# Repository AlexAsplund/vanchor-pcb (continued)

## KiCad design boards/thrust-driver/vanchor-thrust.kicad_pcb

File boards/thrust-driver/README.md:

# vanchor-thrust — trolling-motor DC driver

95×92 mm 2-layer board. Full H-bridge for a 12–24 V brushed trolling motor,
controlled by the vanchor-helm board over one straight 8-wire cable. Two
build variants share the same PCB:

| Variant | Fit | Continuous current |
|---|---|---|
| Base | U1 + U2 (2× BTN8982TA) | ~30 A (with cable reinforcement, see below) |
| High power | also U3 + U4 + R7 + R8 | ~50 A |

## Cable to the helm board

J1 mirrors helm J13 **pin-for-pin** — crimp a straight 8-wire cable
(0.5–1 mm², keep it under ~2 m, twist RPWM/LPWM with GND spares if longer):

| Pin | Signal | Direction |
|---|---|---|
| 1 | RPWM | helm → driver |
| 2 | LPWM | helm → driver |
| 3 | R_EN | helm → driver |
| 4 | L_EN | helm → driver |
| 5 | R_IS (current sense A) | driver → helm |
| 6 | L_IS (current sense B) | driver → helm |
| 7 | +5V (logic, from helm buck) | helm → driver |
| 8 | GND | — |

The LED (D1) lights when the helm's 5 V arrives — a quick cable check.

## Power wiring

M5 lugs: BATT+ / BATT− on the left edge, MOT A / MOT B on the right.
Use 10 mm² (8 AWG) or thicker cable for the 50 A build. **Fuse the battery
lead externally** (ANL or MIDI, 40 A base / 60 A high power) close to the
battery. There is **no reverse-polarity protection** — double-check
polarity before connecting; reversed battery destroys the BTN8982s.
D2 (SMCJ33A) clamps inductive spikes; the board is 12–24 V only.

## Solder-lane reinforcement (required above ~15 A continuous)

The board is ordered in standard 1 oz copper — cheap, but the copper alone
won't carry 30–50 A. Every power lane (VBAT band + spine, MOT A, MOT B on
top; GND band on the bottom) has an exposed solder lane (no solder mask).
Before first high-power use:

1. Clean the lanes with IPA, apply flux.
2. Tin each lane with a wide tip.
3. Lay 4–10 mm² desoldered copper braid or stripped solid wire along the
   lane and solder it down continuously end-to-end.

With braid on all lanes the base build handles ~30 A continuous, the
high-power build ~50 A. The 202 "solder mask bridge" DRC warnings are these
lanes — intentional.

## Firmware note (high-power variant)

Each BTN8982's IS pin sources I_load/kILIS (~8500). Both devices of a side
feed the **same** 1 k sense resistor, so with U3/U4 fitted the sensed
voltage per ampere stays the same only if the halves share evenly — in
practice treat the effective kILIS as ~22700 (verify datasheet 5.4.7) with U1/U2 only and ~17000 per
device (halved reading) when paralleled. Calibrate `THR_IS` scaling in the
Pico firmware after choosing the variant.

## NMEA2000 smart-node option (v1.1 provision, all DNP)

The board carries unpopulated through-hole provision to become a
standalone NMEA2000 node — same pattern as the helm board:

- **U5** Pico 2 (GP12-15 wired in parallel with J1's RPWM/LPWM/R_EN/L_EN,
  GP26/27 read the IS sense via R12/R13 1k series, GP18/19 run CAN via
  can2040 — identical GPIO map to the helm Pico, so the thrust firmware
  ports directly).
- **U6** SIP-3 5V regulator: R-78E5.0-0.5 for 12V boats; fit the wide-input
  **R-78HE5.0-0.5** on 24V boats (the plain R-78E tops out at 28V in, too
  close to a charging 24V bank).
- **J6** 4-pin CAN header: 3V3 / GND / TX / RX to a Waveshare SN65HVD230
  transceiver module; CAN_H/L go to the module's screw terminal.
- **J7** XH-3 lands the N2K drop cable's V+ / GND / SHIELD. R10 (0R DNP)
  optionally feeds the backbone from VBAT (fuse the drop cable); R11
  (0R DNP) bonds shield to GND at this node only if nowhere else does.

Dumb mode (default): populate nothing, drive via the J1 cable as before.
Smart mode: fit U5 + U6 + R12 + R13 + transceiver, **leave J1
unconnected** (both would drive the same nets), and implement a command
watchdog in the node firmware (hard-stop to neutral if the command PGN
stream halts >300-500 ms). ADC note: in normal operation the IS voltage
across the 1k loads stays under ~2.2V at 50A (kILIS 22.7k), but in FAULT
the IS pin sources mA-class current and the node's only protection is the
R12/R13 series resistance - fit them as 10k (not 1k) when populating the
node, or add BAT54S clamps to 3V3 like the helm board has.

## PWM frequency (firmware guidance)

The BTN8982TA allows up to 25 kHz, but this board fits **51 k slew-rate
resistors** (low-EMI edges, ~1.5 us each), so switching loss — not the
chip rating — sets the practical limit. Loss per edge scales with both
current and frequency; conduction loss at 30 A is only ~6 W, so high-kHz
PWM at high current quickly dominates the thermal budget:

```mermaid
xychart-beta
    title "Switching loss vs PWM frequency (13V, 51k SR edges ~3us total)"
    x-axis "PWM frequency (kHz)" [2, 4, 8, 12, 16, 20, 25]
    y-axis "watts" 0 --> 16
    line "at 30 A" [1.2, 2.3, 4.7, 7.0, 9.4, 11.7, 14.6]
    line "at 10 A" [0.4, 0.8, 1.6, 2.3, 3.1, 3.9, 4.9]
```

*[static SVG](../../docs/diagrams/pwm-loss.svg)*

**Recommended scheme: current-adaptive PWM.** Run high frequency where it
is silent *and* cheap (low current), ramp down as current rises so the
bridge stays efficient exactly when the prop is loud enough to mask the
hum:

```mermaid
xychart-beta
    title "Recommended PWM vs motor current"
    x-axis "motor current (A)" [0, 5, 10, 15, 20, 25, 30, 40, 50]
    y-axis "PWM frequency (kHz)" 0 --> 18
    line [16, 16, 12, 8, 6, 5, 4, 3, 2]
```

*[static SVG](../../docs/diagrams/pwm-schedule.svg)*

Implementation notes (RP2350, applies to the helm Pico driving this board
over J13 and to the on-board smart-node Pico alike):

- **Switch on measured current (IS), not throttle** — switching loss
  scales with amps. Use ~2 A hysteresis, or blend continuously per the
  curve above (nicer: the whine fades instead of stepping).
- **Glitch-free frequency changes**: change the PWM slice's wrap (TOP)
  value and rescale the compare level by the same ratio in the same
  update; both latch at the wrap boundary, so duty is preserved and the
  motor never feels a step.
- **Resolution is never the constraint**: 150 MHz / 16 kHz is still >13
  bits of duty resolution.
- **IS sampling**: if sampling mid-on-time, recompute the sample point
  when the wrap changes — or use the RC-averaged reading scaled by duty
  (frequency-agnostic; the helm's 20k + 100n chain does this).
- If the bridge runs warm at partial throttle, lower the 16 kHz band's
  ceiling (~10 A -> ~6 A) before touching hardware. If you truly need
  15-25 kHz at full current, swap R3/R4 (R7/R8) from 51 k to ~5.1 k —
  ~10x less switching loss, more EMI ringing; they are through-hole for
  exactly this experiment.

## Assembly order

1. SMD: BTN8982s (U1/U2, plus U3/U4 for high power), D2.
2. Resistors: R1–R6, R9 (+ R7/R8 with U3/U4), diode D1.
3. C3/C4 ceramics, C5 film, then C1/C2 electrolytics (mind polarity).
4. Lugs J2–J5, header J1.
5. Solder-lane braid (see above), then bolt to a heatsink/baseplate through
   the two M3 holes with a thermal pad under the BTN tabs for >20 A use.

## Ordering

Same fab spec as the helm board: 2 layers, 1.6 mm FR-4, 1 oz copper,
HASL, 5/5 mil, 0.3 mm min drill, tented vias. Upload
`fab/vanchor-thrust-gerbers.zip`. ~$10-15 for 5 pcs at PCBWay/JLC.

## Design notes / DRC deviations

- `solder_mask_bridge` warnings (~200): intentional exposed solder lanes.
- `pth/npth_inside_courtyard`, `courtyards_overlap`: warnings only, from
  the lug/cap density; verified manually.
- `solder_mask_bridge` is set to *ignore* in the project (the exposed
  solder lanes intentionally span nets' mask apertures).
- The routed .kicad_pcb includes hand-placed link tracks and via-hops for
  the DNP-pair nets (RPWM/LPWM/R_EN/L_EN/R_IS/L_IS between U1/U2 and
  U3/U4) — regenerating the board from `scripts/build_board.py` requires
  re-running freerouting **and** re-applying equivalent patches; treat the
  checked-in board file as the source of truth.

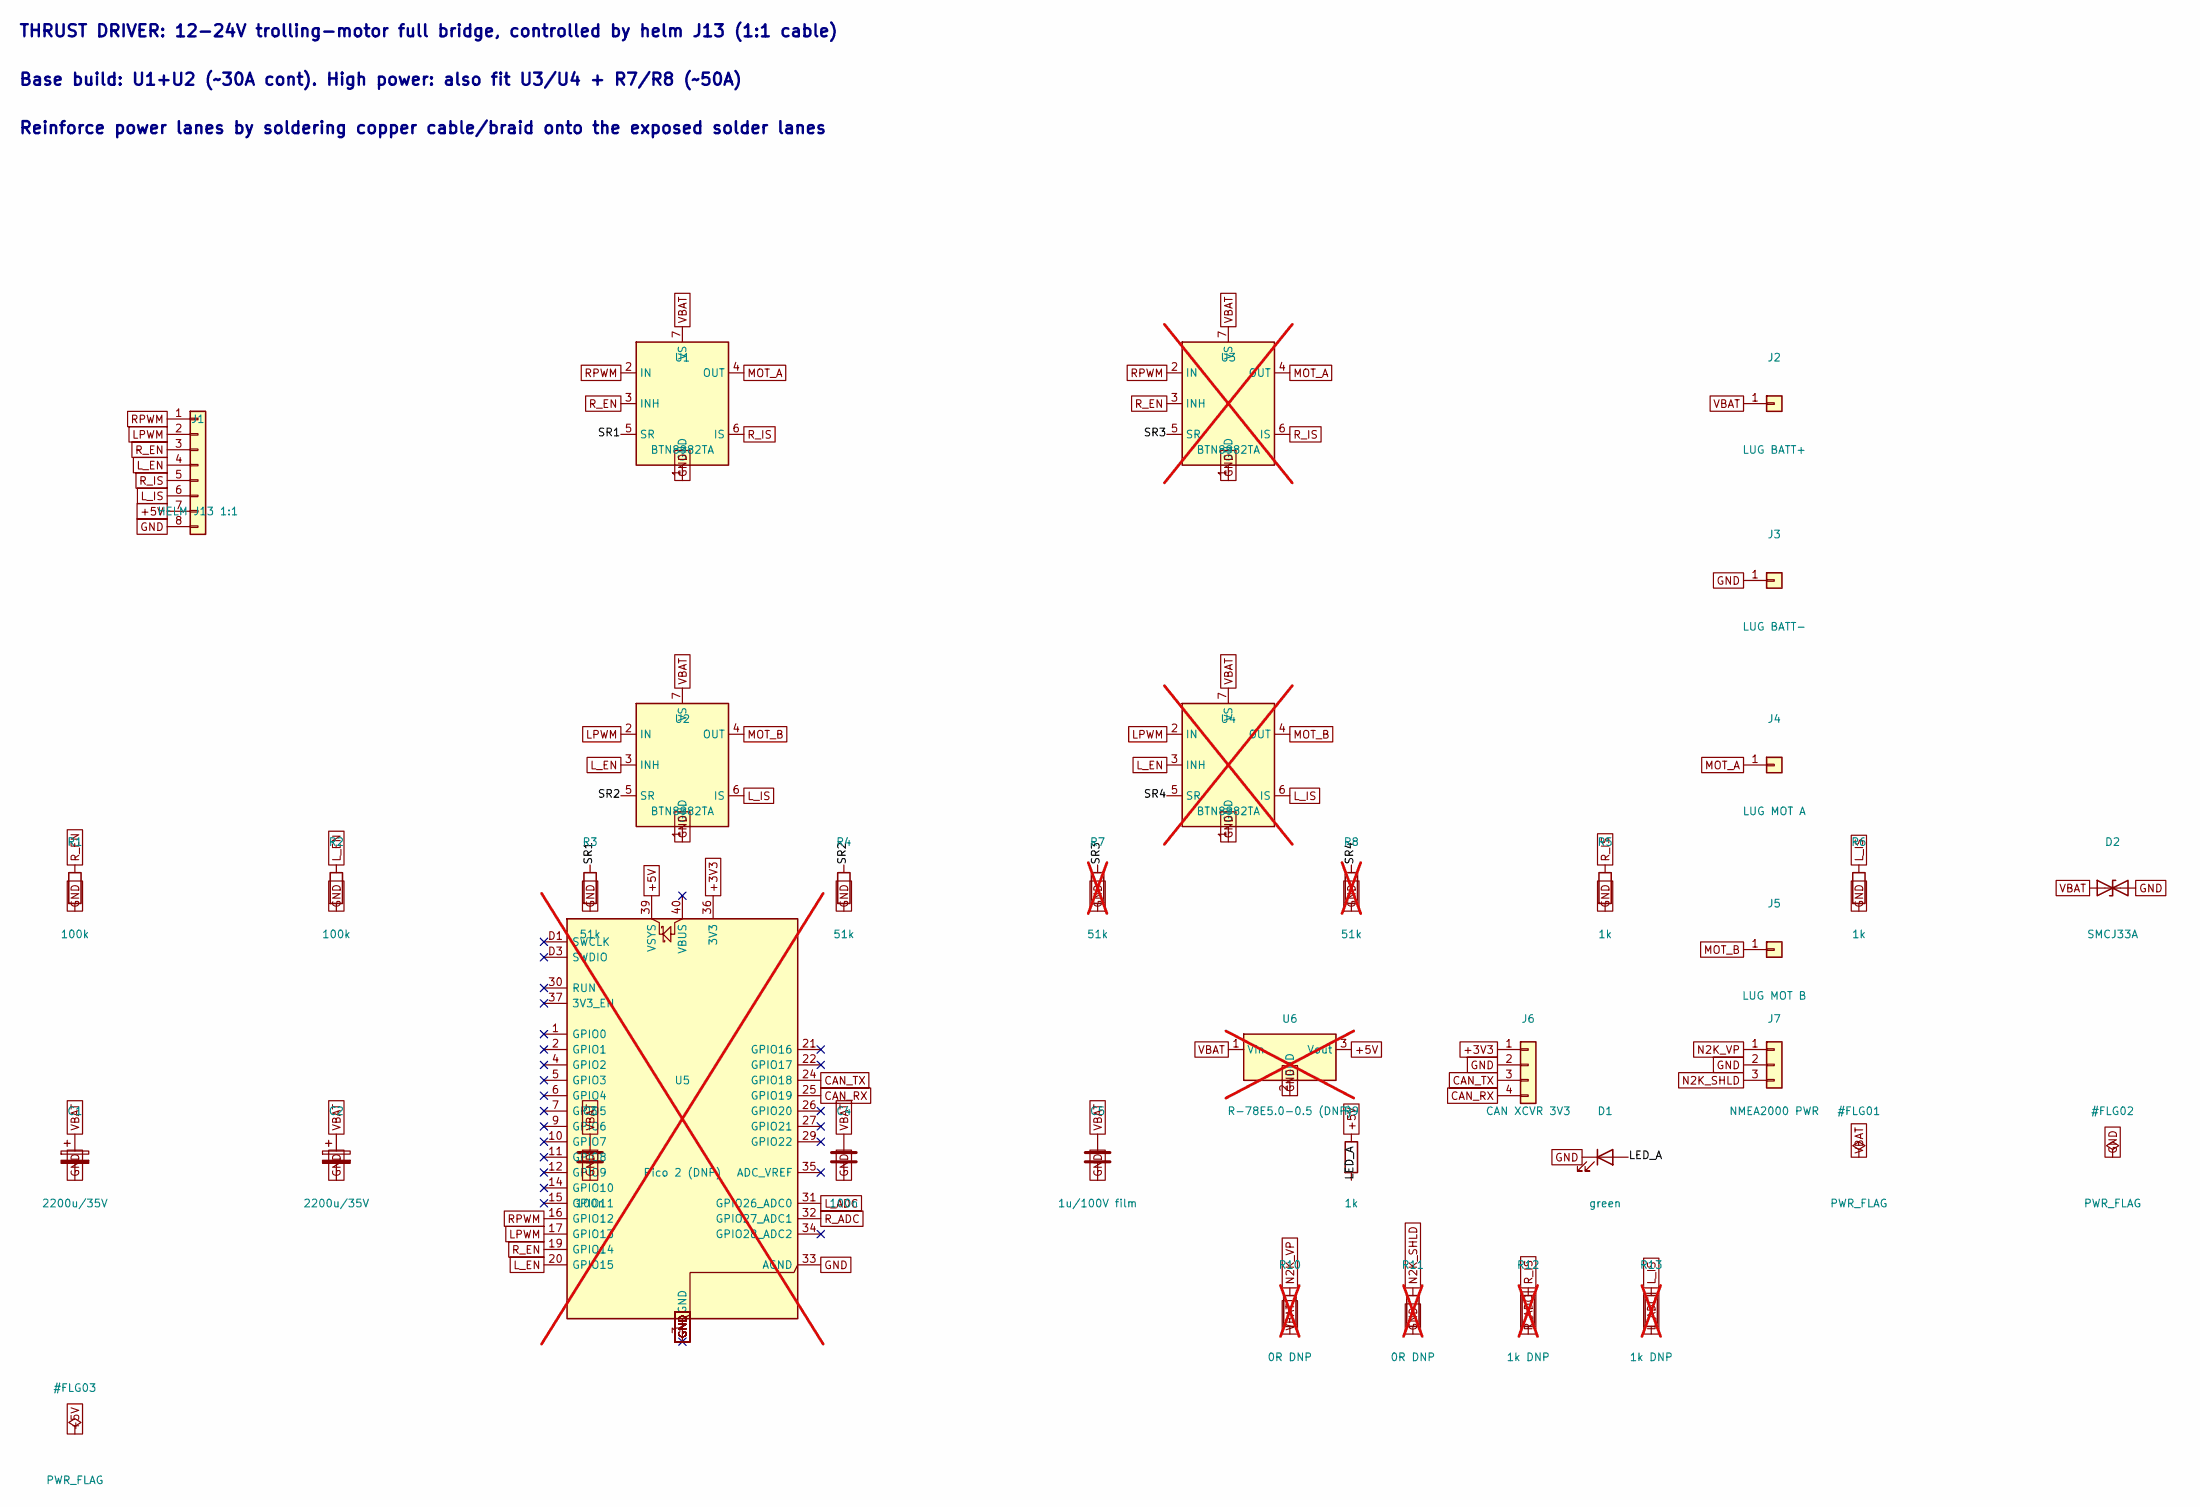
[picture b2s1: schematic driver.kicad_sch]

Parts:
C1, C2: 2200u/35V; CP_Radial_D18.0mm_P7.50mm
C3, C4: 100n; C_Disc_D5.0mm_W2.5mm_P5.00mm
C5: 1u/100V film; C_Rect_L13.0mm_W6.0mm_P10.00mm_FKS3_FKP3_MKS4
D1: green; LED_D5.0mm
D2: SMCJ33A; D_SMC
J1: HELM J13 1:1; PinHeader_1x08_P2.54mm_Vertical
J2: LUG BATT+; Lug_M5
J3: LUG BATT-; Lug_M5
J4: LUG MOT A; Lug_M5
J5: LUG MOT B; Lug_M5
J6: CAN XCVR 3V3; PinHeader_1x04_P2.54mm_Vertical
J7: NMEA2000 PWR; JST_XH_B3B-XH-A_1x03_P2.50mm_Vertical
R1, R2: 100k; R_Axial_DIN0207_L6.3mm_D2.5mm_P10.16mm_Horizontal
R3, R4: 51k; R_Axial_DIN0207_L6.3mm_D2.5mm_P10.16mm_Horizontal
R5, R6, R9: 1k; R_Axial_DIN0207_L6.3mm_D2.5mm_P10.16mm_Horizontal
R7, R8: 51k; R_Axial_DIN0207_L6.3mm_D2.5mm_P10.16mm_Horizontal; not fitted
R10, R11: 0R DNP; R_0805_2012Metric; not fitted
R12, R13: 1k DNP; R_0805_2012Metric; not fitted
U1, U2: BTN8982TA; TO-263-7_TabPin4
U3, U4: BTN8982TA; TO-263-7_TabPin4; not fitted
U5: Pico 2 (DNP); RaspberryPi_Pico_TH_SWD; not fitted
U6: R-78E5.0-0.5 (DNP); Converter_DCDC_TRACO_TSR-1_THT; not fitted

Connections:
+3V3: J6.1, U5.36 (3V3)
+5V: J1.7, R9.1, U5.39 (VSYS), U6.3 (Vout)
/driver/LED_A: D1.2 (A), R9.2
/driver/SR1: R3.1, U1.5 (SR)
/driver/SR2: R4.1, U2.5 (SR)
/driver/SR3: R7.1, U3.5 (SR)
/driver/SR4: R8.1, U4.5 (SR)
CAN_RX: J6.4, U5.25 (GPIO19)
CAN_TX: J6.3, U5.24 (GPIO18)
GND: C1.2, C2.2, C3.2, C4.2, C5.2, D1.1 (K), D2.2 (A2), J1.8, J3.1, J6.2, J7.2, R1.2, R2.2, R3.2, R4.2, R5.2, R6.2, R7.2, R8.2, R11.2, U1.1 (GND), U2.1 (GND), U3.1 (GND), U4.1 (GND), U5.3 (GND), U5.8 (GND), U5.13 (GND), U5.18 (GND), U5.23 (GND), U5.28 (GND), U5.33 (AGND), U5.38 (GND), U5.D2 (GND), U6.2 (GND)
LPWM: J1.2, U2.2 (IN), U4.2 (IN), U5.17 (GPIO13)
L_ADC: R13.2, U5.31 (GPIO26_ADC0)
L_EN: J1.4, R2.1, U2.3 (INH), U4.3 (INH), U5.20 (GPIO15)
L_IS: J1.6, R6.1, R13.1, U2.6 (IS), U4.6 (IS)
MOT_A: J4.1, U1.4 (OUT), U3.4 (OUT)
MOT_B: J5.1, U2.4 (OUT), U4.4 (OUT)
N2K_SHLD: J7.3, R11.1
N2K_VP: J7.1, R10.1
RPWM: J1.1, U1.2 (IN), U3.2 (IN), U5.16 (GPIO12)
R_ADC: R12.2, U5.32 (GPIO27_ADC1)
R_EN: J1.3, R1.1, U1.3 (INH), U3.3 (INH), U5.19 (GPIO14)
R_IS: J1.5, R5.1, R12.1, U1.6 (IS), U3.6 (IS)
VBAT: C1.1, C2.1, C3.1, C4.1, C5.1, D2.1 (A1), J2.1, R10.2, U1.7 (VS), U2.7 (VS), U3.7 (VS), U4.7 (VS), U6.1 (Vin)

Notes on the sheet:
THRUST DRIVER: 12-24V trolling-motor full bridge, controlled by helm J13 (1:1 cable)
Base build: U1+U2 (~30A cont). High power: also fit U3/U4 + R7/R8 (~50A)
Reinforce power lanes by soldering copper cable/braid onto the exposed solder lanes

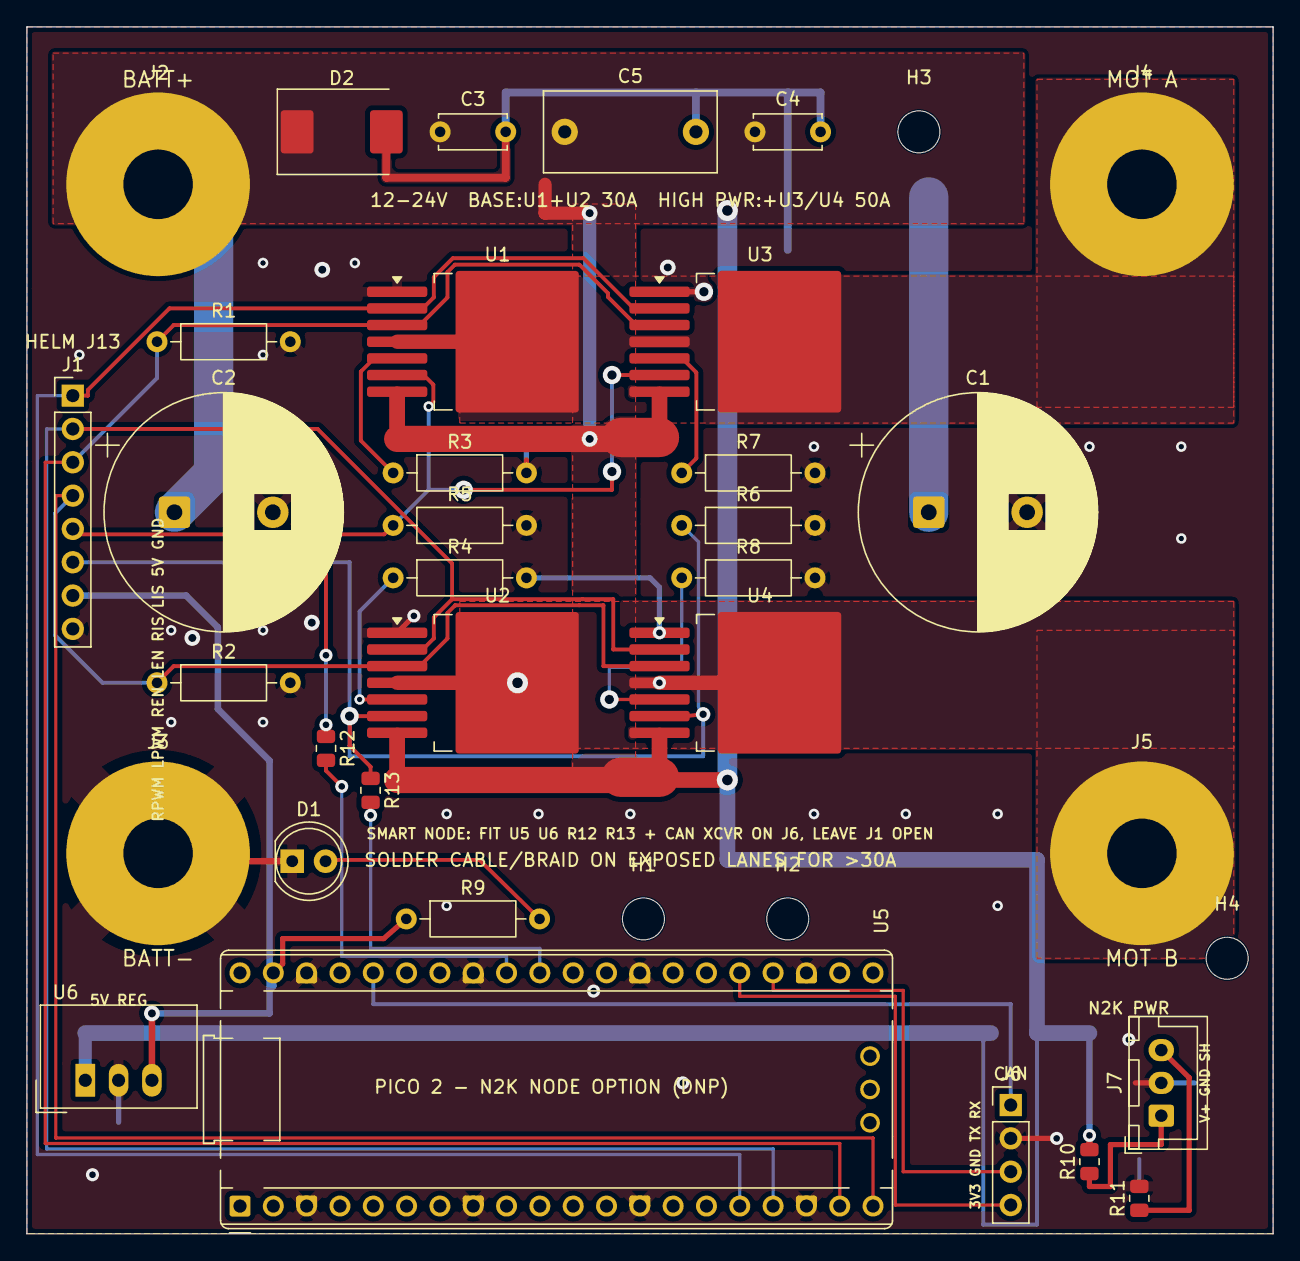
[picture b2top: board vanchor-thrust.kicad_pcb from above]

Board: 2 copper layers, 95.0 x 92.0 mm, 37 parts (0 on the bottom side), 23 nets.

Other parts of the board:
H1, H2: MountingHole_3.2mm_M3
H3, H4: MountingHole; MountingHole_3.2mm_M3

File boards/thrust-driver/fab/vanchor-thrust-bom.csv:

"Ref","Value","Footprint","MPN","Qty","DNP"
"C1,C2","2200u/35V","Capacitor_THT:CP_Radial_D18.0mm_P7.50mm","","2",""
"C3,C4","100n","Capacitor_THT:C_Disc_D5.0mm_W2.5mm_P5.00mm","","2",""
"C5","1u/100V film","Capacitor_THT:C_Rect_L13.0mm_W6.0mm_P10.00mm_FKS3_FKP3_MKS4","","1",""
"D1","green","LED_THT:LED_D5.0mm","","1",""
"D2","SMCJ33A","Diode_SMD:D_SMC","","1",""
"J1","HELM J13 1:1","Connector_PinHeader_2.54mm:PinHeader_1x08_P2.54mm_Vertical","","1",""
"J2","LUG BATT+","vanchor-helm:Lug_M5","","1",""
"J3","LUG BATT-","vanchor-helm:Lug_M5","","1",""
"J4","LUG MOT A","vanchor-helm:Lug_M5","","1",""
"J5","LUG MOT B","vanchor-helm:Lug_M5","","1",""
"J6","CAN XCVR 3V3","Connector_PinHeader_2.54mm:PinHeader_1x04_P2.54mm_Vertical","","1",""
"J7","NMEA2000 PWR","Connector_JST:JST_XH_B3B-XH-A_1x03_P2.50mm_Vertical","","1",""
"R1,R2","100k","Resistor_THT:R_Axial_DIN0207_L6.3mm_D2.5mm_P10.16mm_Horizontal","","2",""
"R3,R4,R7,R8","51k","Resistor_THT:R_Axial_DIN0207_L6.3mm_D2.5mm_P10.16mm_Horizontal","","4","DNP"
"R5,R6,R9","1k","Resistor_THT:R_Axial_DIN0207_L6.3mm_D2.5mm_P10.16mm_Horizontal","","3",""
"R10,R11","0R DNP","Resistor_SMD:R_0805_2012Metric","","2","DNP"
"R12,R13","1k DNP","Resistor_SMD:R_0805_2012Metric","","2","DNP"
"U1-U4","BTN8982TA","Package_TO_SOT_SMD:TO-263-7_TabPin4","","4","DNP"
"U5","Pico 2 (DNP)","vanchor-helm:RaspberryPi_Pico_TH_SWD","","1","DNP"
"U6","R-78E5.0-0.5 (DNP)","Converter_DCDC:Converter_DCDC_TRACO_TSR-1_THT","","1","DNP"

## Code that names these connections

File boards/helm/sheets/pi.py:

"""Orange Pi Zero 3 carrier sheet (v4): 26-pin socket, UART JSTs, spare I2C,
fan, fused aux 5V.

J1 = 2x13 MALE header; the Zero 3 (pre-soldered pins-up variant) connects
via a standard 26-way 1:1 IDC ribbon (original-RPi style). Module is
powered THROUGH the ribbon 5V pins from the on-board buck — no USB-C.
J2 = 1:1 breakout of all 26 pins (DNP). The net map follows the CLASSIC
Raspberry Pi 26-pin positions (the Zero 3 header mimics it), so J2 doubles
as an alternate SBC port: ribbon a Raspberry Pi (pins 1-26 of the 40-pin
header, aligned at pin 1) instead of the Orange Pi. Power, I2C link to the
Pico (RPi SDA1/SCL1), console UART (RPi TXD0/RXD0), SPI and the SWD/RUN
GPIOs all land on equivalent RPi pins. Caveats: fit ONE SBC only (J1 and
J2 share the bus); on an RPi, pins 11/13 (J4 "UART2" JST) are plain GPIOs
- no hardware UART there, use bit-bang or skip J4.

The Zero 3's 26-pin header exposes two usable UARTs (UART5 on PH2/PH3,
UART2 on PC5/PC6) plus TWI3 (I2C) — the Pico link rides TWI3. The H618
debug UART lives on the module's own separate 3-pin header. SWD reflash of
the Pico uses two PC GPIOs (pins 16/18); PICO RUN on pin 12.
"""
from common import HDR2x13, XH2, XH4, HDR1x2, R_AX, LED5MM, POLYFUSE, grid

SHEET_UUID = "c0000000-0000-4000-8000-000000000003"

TEXTS = [
    (30, 40, "ORANGE PI ZERO 3 CARRIER: J1 male header -> 26-way IDC ribbon to the module"),
    (30, 46, "Module is powered through header 5V pins - do NOT also plug USB-C power"),
    (30, 52, "UART TX/RX directions per OPi manual - if a device stays silent, swap TX/RX at the JST"),
    (30, 58, "J2 = same bus, classic RPi 26-pin positions: fits a Raspberry Pi (40-pin header pins 1-26). ONE SBC only"),
]

# Orange Pi Zero 3 26-pin header net map (H618 port in comments)
PI26 = {
    "1": "3V3_PI", "2": "+5V",
    "3": "PI_SDA",            # PH5  TWI3-SDA -> Pico
    "4": "+5V",
    "5": "PI_SCL",            # PH4  TWI3-SCK -> Pico
    "6": "GND",
    "7": "OPI_PC9",
    "8": "UART5_TX",          # PH2
    "9": "GND",
    "10": "UART5_RX",         # PH3
    "11": "UART2_TX",         # PC6 (check DT overlay; swap at JST if needed)
    "12": "PI_PICO_RUN",      # PC11 -> Pico RUN (reset)
    "13": "UART2_RX",         # PC5
    "14": "GND",
    "15": "OPI_PC8",
    "16": "PI_GPIO24",        # PC15 -> Pico SWDIO
    "17": "3V3_PI",
    "18": "PI_GPIO25",        # PC14 -> Pico SWCLK
    "19": "OPI_MOSI",         # PH7  SPI1
    "20": "GND",
    "21": "OPI_MISO",         # PH8
    "22": "OPI_PC7",
    "23": "OPI_SCLK",         # PH6
    "24": "OPI_CS",           # PH9
    "25": "GND",
    "26": "OPI_PC10",
}

# Ground economy: J1.14, J1.20 and J2.9 are deliberately NC — each connector keeps
# four other GND pins (6/9/20/25 resp. 6/14/20/25); the escape routing under
# the header field claims those two pads' corridors.
J1_PINS = dict(PI26, **{"14": None, "20": None})
J2_PINS = dict(PI26, **{"9": None})

COMPONENTS = [
    dict(lib="Connector_Generic:Conn_02x13_Odd_Even", ref="J1", value="OPI_Z3_26PIN",
         fp=HDR2x13, at=(70, 95, 0), pins=J1_PINS),
    dict(lib="Connector_Generic:Conn_02x13_Odd_Even", ref="J2", value="SBC2_OPI_RPI26", dnp=True,
         fp=HDR2x13, at=(150, 95, 0), pins=J2_PINS),

    dict(lib="Connector_Generic:Conn_01x04", ref="J3", value="UART5 ttyAS5", fp=XH4,
         at=(230, 70, 0), pins={"1": "3V3_PI", "2": "UART5_TX", "3": "UART5_RX", "4": "GND"}),
    dict(lib="Connector_Generic:Conn_01x04", ref="J4", value="UART2 ttyAS2", fp=XH4,
         at=(260, 70, 0), pins={"1": "3V3_PI", "2": "UART2_TX", "3": "UART2_RX", "4": "GND"}),

    dict(lib="Connector_Generic:Conn_01x04", ref="J8", value="I2C3 spare", fp=XH4,
         at=(230, 120, 0), pins={"1": "3V3_PI", "2": "PI_SDA", "3": "PI_SCL", "4": "GND"}),
    dict(lib="Device:R", ref="R5", value="2.2k", fp=R_AX, dnp=True,
         at=(260, 120, 0), pins={"1": "3V3_PI", "2": "PI_SDA"}),
    dict(lib="Device:R", ref="R6", value="2.2k", fp=R_AX, dnp=True,
         at=(290, 120, 0), pins={"1": "3V3_PI", "2": "PI_SCL"}),

    dict(lib="Connector_Generic:Conn_01x03", ref="J9", value="FAN + HALL",
         fp="Connector_PinHeader_2.54mm:PinHeader_1x03_P2.54mm_Vertical",
         at=(320, 120, 0), pins={"1": "+5V", "2": "GND", "3": "HALL_ZERO"}),
    dict(lib="Device:Polyfuse", ref="F2", value="MF-R250 2.5A", fp=POLYFUSE,
         at=(350, 120, 0), pins={"1": "+5V", "2": "DISP_5V"}),
    dict(lib="Connector_Generic:Conn_01x02", ref="J10", value="AUX 5V (screen)", fp=XH2,
         at=(380, 120, 0), pins={"1": "DISP_5V", "2": "GND"}),

    dict(lib="power:PWR_FLAG", ref="#FLG04", value="PWR_FLAG",
         at=grid(2), pins={"1": "3V3_PI"}),
]

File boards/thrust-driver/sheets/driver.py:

"""Thrust driver board: 12-24V full-bridge for the trolling motor.

One sheet. J1 mirrors the helm board's J13 pin-for-pin (IBT-2 order), so a
straight 8-wire cable connects them. U1/U2 = base bridge (~30A cont);
U3/U4 + their SR resistors = DNP parallel pair for the high-power build
(fit for ~50A sustained; both pairs share IN/INH, each device has its own
slew-rate resistor; IS current sources sum into the shared 1k loads so the
helm's telemetry scaling is unchanged per-variant... halved kILIS effective
- note in firmware calibration).
"""
from common import R_AX, C_D, CP_BULK, SMC, TO263_7, HDR1x8, LED5MM, LUG, FILM, grid

SHEET_UUID = "d0000000-0000-4000-8000-000000000002"

TEXTS = [
    (30, 30, "THRUST DRIVER: 12-24V trolling-motor full bridge, controlled by helm J13 (1:1 cable)"),
    (30, 38, "Base build: U1+U2 (~30A cont). High power: also fit U3/U4 + R7/R8 (~50A)"),
    (30, 46, "Reinforce power lanes by soldering copper cable/braid onto the exposed solder lanes"),
]

COMPONENTS = [
    # control interface - identical pinout to helm J13
    dict(lib="Connector_Generic:Conn_01x08", ref="J1", value="HELM J13 1:1", fp=HDR1x8,
         at=(45, 95, 0), pins={
            "1": "RPWM", "2": "LPWM", "3": "R_EN", "4": "L_EN",
            "5": "R_IS", "6": "L_IS", "7": "+5V", "8": "GND"}),
    dict(lib="Device:R", ref="R1", value="100k", fp=R_AX,
         at=(130, 195, 90), pins={"1": "R_EN", "2": "GND"}),
    dict(lib="Device:R", ref="R2", value="100k", fp=R_AX,
         at=(174, 195, 90), pins={"1": "L_EN", "2": "GND"}),

    # base bridge
    dict(lib="vanchor-helm:BTN8982TA", ref="U1", value="BTN8982TA", fp=TO263_7,
         at=(135, 80, 0), pins={"1": "GND", "2": "RPWM", "3": "R_EN",
                                "4": "MOT_A", "5": ".SR1", "6": "R_IS", "7": "VBAT"}),
    dict(lib="vanchor-helm:BTN8982TA", ref="U2", value="BTN8982TA", fp=TO263_7,
         at=(135, 150, 0), pins={"1": "GND", "2": "LPWM", "3": "L_EN",
                                 "4": "MOT_B", "5": ".SR2", "6": "L_IS", "7": "VBAT"}),
    dict(lib="Device:R", ref="R3", value="51k", fp=R_AX,
         at=(218, 195, 90), pins={"1": ".SR1", "2": "GND"}),
    dict(lib="Device:R", ref="R4", value="51k", fp=R_AX,
         at=(262, 195, 90), pins={"1": ".SR2", "2": "GND"}),

    # high-power parallel pair (DNP on base builds)
    dict(lib="vanchor-helm:BTN8982TA", ref="U3", value="BTN8982TA", fp=TO263_7, dnp=True,
         at=(225, 80, 0), pins={"1": "GND", "2": "RPWM", "3": "R_EN",
                                "4": "MOT_A", "5": ".SR3", "6": "R_IS", "7": "VBAT"}),
    dict(lib="vanchor-helm:BTN8982TA", ref="U4", value="BTN8982TA", fp=TO263_7, dnp=True,
         at=(225, 150, 0), pins={"1": "GND", "2": "LPWM", "3": "L_EN",
                                 "4": "MOT_B", "5": ".SR4", "6": "L_IS", "7": "VBAT"}),
    dict(lib="Device:R", ref="R7", value="51k", fp=R_AX, dnp=True,
         at=(306, 195, 90), pins={"1": ".SR3", "2": "GND"}),
    dict(lib="Device:R", ref="R8", value="51k", fp=R_AX, dnp=True,
         at=(130, 220, 90), pins={"1": ".SR4", "2": "GND"}),

    # IS loads: current-source outputs develop the sense voltage here
    dict(lib="Device:R", ref="R5", value="1k", fp=R_AX,
         at=(174, 220, 90), pins={"1": "R_IS", "2": "GND"}),
    dict(lib="Device:R", ref="R6", value="1k", fp=R_AX,
         at=(218, 220, 90), pins={"1": "L_IS", "2": "GND"}),

    # power conditioning
    dict(lib="Device:D_TVS", ref="D2", value="SMCJ33A", fp=SMC,
         at=(322, 190, 0), pins={"1": "VBAT", "2": "GND"}),
    dict(lib="Device:C_Polarized", ref="C1", value="2200u/35V", fp=CP_BULK,
         at=(218, 245, 90), pins={"1": "VBAT", "2": "GND"}),
    dict(lib="Device:C_Polarized", ref="C2", value="2200u/35V", fp=CP_BULK,
         at=(258, 245, 90), pins={"1": "VBAT", "2": "GND"}),
    dict(lib="Device:C", ref="C3", value="100n", fp=C_D,
         at=(262, 220, 90), pins={"1": "VBAT", "2": "GND"}),
    dict(lib="Device:C", ref="C4", value="100n", fp=C_D,
         at=(306, 220, 90), pins={"1": "VBAT", "2": "GND"}),
    dict(lib="Device:C", ref="C5", value="1u/100V film", fp=FILM,
         at=(130, 245, 90), pins={"1": "VBAT", "2": "GND"}),

    # cable-live indicator off the helm's 5V
    dict(lib="Device:R", ref="R9", value="1k", fp=R_AX,
         at=(174, 245, 90), pins={"1": "+5V", "2": ".LED_A"}),
    dict(lib="Device:LED", ref="D1", value="green", fp=LED5MM,
         at=(374, 168, 0), pins={"2": ".LED_A", "1": "GND"}),

    # ---- NMEA2000 node provision (ALL DNP: holes only, populate later) ----
    # Smart-node mode: fit U5 (Pico 2), U6 (TSR-1/R-78E5.0 SIP-3 regulator),
    # R12/R13 (1k ADC series) and a 3.3V CAN transceiver on J6; the node then
    # self-powers from VBAT and takes commands over NMEA2000 (can2040 on
    # GP18/GP19). Leave J1 unconnected in that mode. Dumb mode: leave all of
    # this unpopulated and drive via J1 as today. Same GPIO map as the helm
    # Pico: GP12-15 drive, GP26/27 sense, GP18/19 CAN.
    dict(lib="MCU_Module:RaspberryPi_Pico_Debug", ref="U5", value="Pico 2 (DNP)", dnp=True,
         fp="vanchor-helm:RaspberryPi_Pico_TH_SWD",
         at=(70, 238, 0), pins={
            "3": "GND", "8": "GND", "13": "GND", "18": "GND", "23": "GND",
            "28": "GND", "33": "GND", "38": "GND",
            "16": "RPWM", "17": "LPWM", "19": "R_EN", "20": "L_EN",
            "24": "CAN_TX", "25": "CAN_RX",
            "31": "L_ADC", "32": "R_ADC",
            "36": "+3V3", "39": "+5V",
            **{str(n): None for n in (1, 2, 4, 5, 6, 7, 9, 10, 11, 12, 14, 15,
                                      21, 22, 26, 27, 29, 30, 34, 35, 37, 40)},
            "D1": None, "D2": None, "D3": None}),
    dict(lib="Converter_DCDC:TSR_1-2450", ref="U6", value="R-78E5.0-0.5 (DNP)", dnp=True,
         fp="Converter_DCDC:Converter_DCDC_TRACO_TSR-1_THT",
         at=(374, 195, 0), pins={"1": "VBAT", "2": "GND", "3": "+5V"}),
    dict(lib="Connector_Generic:Conn_01x04", ref="J6", value="CAN XCVR 3V3", fp=HDR1x8.replace("1x08", "1x04"),
         at=(330, 222, 0), pins={"1": "+3V3", "2": "GND", "3": "CAN_TX", "4": "CAN_RX"}),
    dict(lib="Connector_Generic:Conn_01x03", ref="J7", value="NMEA2000 PWR",
         fp="Connector_JST:JST_XH_B3B-XH-A_1x03_P2.50mm_Vertical",
         at=(374, 222, 0), pins={"1": "N2K_VP", "2": "GND", "3": "N2K_SHLD"}),
    dict(lib="Device:R", ref="R10", value="0R DNP", dnp=True,
         fp="Resistor_SMD:R_0805_2012Metric",
         at=(130, 267, 90), pins={"1": "N2K_VP", "2": "VBAT"}),
    dict(lib="Device:R", ref="R11", value="0R DNP", dnp=True,
         fp="Resistor_SMD:R_0805_2012Metric",
         at=(172, 267, 90), pins={"1": "N2K_SHLD", "2": "GND"}),
    dict(lib="Device:R", ref="R12", value="1k DNP", dnp=True,
         fp="Resistor_SMD:R_0805_2012Metric",
         at=(214, 267, 90), pins={"1": "R_IS", "2": "R_ADC"}),
    dict(lib="Device:R", ref="R13", value="1k DNP", dnp=True,
         fp="Resistor_SMD:R_0805_2012Metric",
         at=(254, 267, 90), pins={"1": "L_IS", "2": "L_ADC"}),

    # power lugs
    dict(lib="Connector_Generic:Conn_01x01", ref="J2", value="LUG BATT+", fp=LUG,
         at=(330, 75, 0), pins={"1": "VBAT"}),
    dict(lib="Connector_Generic:Conn_01x01", ref="J3", value="LUG BATT-", fp=LUG,
         at=(330, 105, 0), pins={"1": "GND"}),
    dict(lib="Connector_Generic:Conn_01x01", ref="J4", value="LUG MOT A", fp=LUG,
         at=(330, 135, 0), pins={"1": "MOT_A"}),
    dict(lib="Connector_Generic:Conn_01x01", ref="J5", value="LUG MOT B", fp=LUG,
         at=(330, 165, 0), pins={"1": "MOT_B"}),

    dict(lib="power:PWR_FLAG", ref="#FLG01", value="PWR_FLAG",
         at=(330, 42, 0), pins={"1": "VBAT"}),
    dict(lib="power:PWR_FLAG", ref="#FLG02", value="PWR_FLAG",
         at=(352, 42, 0), pins={"1": "GND"}),
    dict(lib="power:PWR_FLAG", ref="#FLG03", value="PWR_FLAG",
         at=(374, 42, 0), pins={"1": "+5V"}),
]

WIRES = [
    # DNP Pico smart-node hookup: CAN pair to the transceiver header,
    # IS sense through the 1k series resistors to the ADCs
    (("U5", "24"), ("J6", "3"), [("x", 106.68), ("y", 280.67), ("x", 283.21), ("y", 223.27)]),
    (("U5", "25"), ("J6", "4"), [("x", 104.14), ("y", 283.21), ("x", 287.02), ("y", 225.81)]),
    (("U5", "31"), ("R13", "2"), [("x", 111.76), ("y", 262.89)]),
    (("U5", "32"), ("R12", "2"), [("x", 109.22), ("y", 264.16)]),
]

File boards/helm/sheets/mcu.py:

"""Pico 2 controller sheet: I2C slave to Pi, I2C master to AS5600, PWM to
H-bridge, digipot/contactor control lines, battery telemetry, utility header.

Pin allocation per plan (Pico 2 module is pin-compatible with the Pico symbol).
"""
from common import PICO_FP, R_AX, C_D, SOT23, LED5MM, HDR1x8, grid

SHEET_UUID = "c0000000-0000-4000-8000-000000000004"

TEXTS = [
    (30, 40, "MCU: Pico 2 (RP2350) - I2C0 slave @0x42 to Pi, I2C1 master to AS5600"),
    (30, 46, "Firmware map: 0x00 CMD {pwm,dir,steer} / 0x10 STATUS {angle,ok,wrap,state,vbat,isense}; 800ms watchdog"),
    (30, 52, "Pico soldered directly (low profile, sits under the Pi). Pi reflashes it via SWD on GPIO24/25 (openocd)."),
]

COMPONENTS = [
    dict(lib="MCU_Module:RaspberryPi_Pico_Debug", ref="U1", value="Pico 2", fp=PICO_FP,
         at=(80, 110, 0), pins={
            "1": "PICO_GP0", "2": "PICO_GP1", "3": "GND",
            "4": "PICO_GP2", "5": "PICO_GP3",
            "6": "PI_SDA", "7": "PI_SCL", "8": "GND",
            "9": "ENC_SDA", "10": "ENC_SCL",
            "11": "RPWM", "12": "LPWM", "13": "GND",
            "14": "R_EN", "15": "L_EN",
            "16": "THR_RPWM", "17": "THR_LPWM", "18": "GND",
            "19": "THR_R_EN", "20": "THR_L_EN",
            "21": None, "22": "LED_STAT", "23": "GND",
            "24": "PICO_GP18", "25": "PICO_GP19", "26": None,
            "27": None, "28": "GND", "29": None,  # GP20-22 unused
            "30": ".PICO_RUN",
            "31": "SERVO_IS", "32": "THR_IS",
            "33": "GND", "34": "VBAT_SENSE",
            "35": None,          # ADC_VREF: module's onboard filter
            "36": "+3V3", "37": None,  # 3V3_EN: pulled up on module
            "38": "GND", "39": "+5V", "40": None,  # VBUS unused (no USB power in)
            "D1": "PI_GPIO25",   # SWCLK <- Pi (openocd bcm2835gpio reflash)
            "D2": "GND",
            "D3": "PI_GPIO24",   # SWDIO <-> Pi
         }),

    dict(lib="Device:R", ref="R8", value="1k", fp=R_AX,
         at=grid(0), pins={"1": "PI_PICO_RUN", "2": ".PICO_RUN"}),
    dict(lib="Device:R", ref="R9", value="4.7k", fp=R_AX,
         at=grid(1), pins={"1": "+3V3", "2": "ENC_SDA"}),
    dict(lib="Device:R", ref="R10", value="4.7k", fp=R_AX,
         at=grid(2), pins={"1": "+3V3", "2": "ENC_SCL"}),

    # Battery voltage telemetry: 47k/10k = /5.7 -> 14.4V charging reads 2.53V
    dict(lib="Device:R", ref="R11", value="47k", fp=R_AX,
         at=grid(3), pins={"1": "VIN", "2": "VBAT_SENSE"}),
    dict(lib="Device:R", ref="R12", value="10k", fp=R_AX,
         at=grid(4), pins={"1": "VBAT_SENSE", "2": "GND"}),
    dict(lib="Device:C", ref="C5", value="100n", fp=C_D,
         at=grid(5), pins={"1": "VBAT_SENSE", "2": "GND"}),
    dict(lib="Diode:BAT54S", ref="D6", value="BAT54S", fp=SOT23,
         at=grid(6), pins={"1": "GND", "2": "+3V3", "3": "VBAT_SENSE"}),

    dict(lib="Device:R", ref="R13", value="1k", fp=R_AX,
         at=grid(7), pins={"1": "LED_STAT", "2": ".LED5_A"}),
    dict(lib="Device:LED", ref="LED5", value="yellow", fp=LED5MM,
         at=grid(8), pins={"2": ".LED5_A", "1": "GND"}),

    # steering zero/index hall switch (A3144 class, open collector) shares
    # J9 (FAN header grows 1x2 -> 1x3: 5V GND SIG). 10k pullup to 3V3 (the
    # line can never exceed 3V3), 100n filter, 1k series into GP0 (also on J12.2
    # as a breakout/test point; UART0 fallback moves to GP16/GP1).
    dict(lib="Device:R", ref="R22", value="10k",
         fp="Resistor_SMD:R_0805_2012Metric",
         at=(230, 150, 0), pins={"1": "HALL_ZERO", "2": "+3V3"}),
    dict(lib="Device:R", ref="R23", value="1k",
         fp="Resistor_SMD:R_0805_2012Metric",
         at=(260, 150, 0), pins={"1": "HALL_ZERO", "2": "PICO_GP0"}),
    dict(lib="Device:C", ref="C24", value="100n",
         fp="Capacitor_SMD:C_0805_2012Metric",
         at=(290, 150, 0), pins={"1": "HALL_ZERO", "2": "GND"}),

    dict(lib="Connector_Generic:Conn_01x08", ref="J12", value="PICO UTIL", fp=HDR1x8, dnp=True,
         at=(200, 110, 0), pins={
            "1": "+3V3", "2": "PICO_GP0", "3": "PICO_GP1", "4": "PICO_GP2",
            "5": "PICO_GP3", "6": "PICO_GP18", "7": "PICO_GP19", "8": "GND"}),
]

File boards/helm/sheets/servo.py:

"""Servo sheet: ON-BOARD H-bridge (2x BTN8982TA half-bridges) for the 12V worm
gearmotor + the cabled AS5600 encoder connector (I2C1).

The BTN8982 pair speaks the exact BTS7960/IBT-2 interface the vanchor-ng
steering firmware already uses: RPWM/LPWM into IN, R_EN/L_EN into INH,
combined IS through one 1k sense resistor (only the driving side sources
current) filtered + clamped into the Pico ADC. VM = +12V rail.
"""
from common import XH2, XH4, TB2, R_AX, C_D, SOT23, grid

SHEET_UUID = "c0000000-0000-4000-8000-000000000006"

TEXTS = [
    (30, 40, "SERVO: on-board 2x BTN8982TA half-bridge (BTS7960-compatible interface), VM = +12V rail"),
    (30, 46, "AS5600 (in servo housing per vanchor-ng cad/) cabled to J11; keep lead <1m, 100kHz"),
    (30, 52, "24-48V boats: servo stall limited by BUCK2 (4.5A). 12V boats: J17 links VIN->12V, full stall current"),
]

COMPONENTS = [
    dict(lib="vanchor-helm:BTN8982TA", ref="U7", value="BTN8982TA",
         fp="Package_TO_SOT_SMD:TO-263-7_TabPin4",
         at=(70, 100, 0), pins={
            "1": "GND", "2": "RPWM", "3": "R_EN",
            "4": "SERVO_A", "5": ".SR_A", "6": ".SERVO_IS_RAW", "7": "VIN"}),
    dict(lib="vanchor-helm:BTN8982TA", ref="U8", value="BTN8982TA",
         fp="Package_TO_SOT_SMD:TO-263-7_TabPin4",
         at=(130, 100, 0), pins={
            "1": "GND", "2": "LPWM", "3": "L_EN",
            "4": "SERVO_B", "5": ".SR_B", "6": ".SERVO_IS_RAW", "7": "VIN"}),
    dict(lib="Device:R", ref="R39", value="47k", fp=R_AX,     # slew-rate set
         at=grid(0), pins={"1": ".SR_A", "2": "GND"}),
    dict(lib="Device:R", ref="R40", value="47k", fp=R_AX,
         at=grid(1), pins={"1": ".SR_B", "2": "GND"}),
    dict(lib="Device:C_Polarized", ref="C22", value="220u/25V",
         fp="Capacitor_THT:CP_Radial_D8.0mm_P3.50mm",
         at=grid(2), pins={"1": "VIN", "2": "GND"}),
    dict(lib="Device:C", ref="C23", value="100n", fp=C_D,
         at=grid(3), pins={"1": "VIN", "2": "GND"}),
    dict(lib="Connector_Generic:Conn_01x02", ref="J22", value="SERVO MOTOR", fp=TB2,
         at=(200, 100, 0), pins={"1": "SERVO_A", "2": "SERVO_B"}),

    # combined current sense: IS pins -> 1k to GND, filtered + clamped to ADC
    dict(lib="Device:R", ref="R19", value="1k", fp=R_AX,
         at=grid(4), pins={"1": ".SERVO_IS_RAW", "2": "GND"}),
    dict(lib="Device:R", ref="R18", value="10k", fp=R_AX,
         at=grid(5), pins={"1": ".SERVO_IS_RAW", "2": "SERVO_IS"}),
    dict(lib="Diode:BAT54S", ref="D8", value="BAT54S", fp=SOT23,
         at=grid(6), pins={"1": "GND", "2": "+3V3", "3": "SERVO_IS"}),
    dict(lib="Device:C", ref="C12", value="100n", fp=C_D,
         at=grid(7), pins={"1": "SERVO_IS", "2": "GND"}),

    # AS5600 encoder connector (unchanged)
    dict(lib="Device:R", ref="R20", value="100R", fp=R_AX,
         at=grid(8), pins={"1": "ENC_SDA", "2": ".ENC_SDA_J"}),
    dict(lib="Device:R", ref="R21", value="100R", fp=R_AX,
         at=grid(9), pins={"1": "ENC_SCL", "2": ".ENC_SCL_J"}),
    dict(lib="Diode:BAT54S", ref="D10", value="BAT54S", fp=SOT23,
         at=grid(10), pins={"1": "GND", "2": "+3V3", "3": ".ENC_SDA_J"}),
    dict(lib="Diode:BAT54S", ref="D11", value="BAT54S", fp=SOT23,
         at=grid(11), pins={"1": "GND", "2": "+3V3", "3": ".ENC_SCL_J"}),
    dict(lib="Connector_Generic:Conn_01x04", ref="J11", value="AS5600", fp=XH4,
         at=(200, 140, 0), pins={"1": "+3V3", "2": "GND", "3": ".ENC_SDA_J", "4": ".ENC_SCL_J"}),
]

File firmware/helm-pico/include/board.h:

/*
 * board.h — helm board v4.2 pin map + tuning for the on-board Pico 2.
 *
 * Pin numbers are RP2350 GPIOs; the net names match the schematic
 * (boards/helm/sheets/mcu.py) and docs/HANDOFF.md. Anything marked
 * CALIBRATE has a bench procedure in the firmware README.
 *
 * DIY / bare-Pico builds: every #define below is #ifndef-guarded, so any pin
 * or default can be overridden from the build instead of editing this file:
 *   cmake -B build -DPICO_BOARD=pico \
 *     -DCMAKE_CXX_FLAGS="-DPIN_LED_STAT=25 -DTUN_I2C_ADDR=0x42"
 * See README "Bare Pico / DIY build" for the wiring that goes with it —
 * especially the EXTERNAL pulldowns on the four EN pins: the firmware cannot
 * protect the reset/BOOTSEL window, only resistors can.
 */
#ifndef HELM_BOARD_H
#define HELM_BOARD_H

// ---------------------------------------------------------------- inputs --
#ifndef PIN_HALL_ZERO
#define PIN_HALL_ZERO      0   // HALL_ZERO: open-collector hall (J9.3), 10k
#endif
                               // pull-up + RC on board; LOW at the magnet.

// I2C0 to the SBC (PI_SDA/PI_SCL on the ribbon): line-protocol tunnel,
// slave address 0x42 — equivalent to the USB CDC port (docs/I2C-TUNNEL.md).
#ifndef PIN_PI_SDA
#define PIN_PI_SDA         4
#endif
#ifndef PIN_PI_SCL
#define PIN_PI_SCL         5
#endif

// I2C1 master -> AS5600 steering encoder (J11; 4.7k pull-ups R9/R10 on board)
#ifndef PIN_ENC_SDA
#define PIN_ENC_SDA        6
#endif
#ifndef PIN_ENC_SCL
#define PIN_ENC_SCL        7
#endif
#ifndef ENC_I2C
#define ENC_I2C            i2c1
#endif
#ifndef ENC_I2C_HZ
#define ENC_I2C_HZ         400000
#endif

// -------------------------------------------------------- servo H-bridge --
// 2x BTN8982TA on protected VIN. IN = PWM, INH = enable (100k pulldowns on
// board keep the bridge disabled whenever the Pico is dead or rebooting).
#ifndef PIN_SRV_RPWM
#define PIN_SRV_RPWM       8   // U7 IN  (drive toward +deg / starboard)
#endif
#ifndef PIN_SRV_LPWM
#define PIN_SRV_LPWM       9   // U8 IN  (drive toward -deg / port)
#endif
#ifndef PIN_SRV_R_EN
#define PIN_SRV_R_EN      10   // U7 INH
#endif
#ifndef PIN_SRV_L_EN
#define PIN_SRV_L_EN      11   // U8 INH
#endif

// ------------------------------------------------- thrust bridge on J13 --
// 8-wire cable to the companion thrust-driver board (IBT-2 pin order).
#ifndef PIN_THR_RPWM
#define PIN_THR_RPWM      12
#endif
#ifndef PIN_THR_LPWM
#define PIN_THR_LPWM      13
#endif
#ifndef PIN_THR_R_EN
#define PIN_THR_R_EN      14
#endif
#ifndef PIN_THR_L_EN
#define PIN_THR_L_EN      15
#endif

#ifndef PIN_LED_STAT
#define PIN_LED_STAT      17   // yellow LED via R13 (bare Pico: use 25 = onboard LED)
#endif

// ------------------------------------------------------------------ ADCs --
#ifndef PIN_ADC_SERVO_IS
#define PIN_ADC_SERVO_IS  26   // ADC0: servo bridge current sense
#endif
#ifndef PIN_ADC_THR_IS
#define PIN_ADC_THR_IS    27   // ADC1: thrust driver current sense (mixed R/L)
#endif
#ifndef PIN_ADC_VBAT
#define PIN_ADC_VBAT      28   // ADC2: VBAT through 47k/10k divider
#endif

#ifndef ADC_VREF_V
#define ADC_VREF_V        3.3f
#endif
// VBAT divider R11 47k / R12 10k  ->  Vbat = Vadc * 5.7
#ifndef VBAT_SCALE
#define VBAT_SCALE        ((47.0f + 10.0f) / 10.0f)
#endif
// Thrust IS: BTN8982 kILIS ~= 22700; 1k loads at the driver, 1k series +
// 20k to GND on the helm. Simulated end-to-end: ~21 mV per motor amp
// (sim/README.md). CALIBRATE against a clamp meter before trusting it.
#ifndef THR_IS_V_PER_A
#define THR_IS_V_PER_A    0.021f
#endif
// Servo IS: RAW node 1k load (R19), so ~44 mV/A before the R18/C12 filter.
#ifndef SERVO_IS_V_PER_A
#define SERVO_IS_V_PER_A  0.044f
#endif

// ------------------------------------------------------- steering tuning --
// DEFAULTS ONLY from here down: every value below is runtime-tunable over
// the serial port (CONF/CONFW/CONFSAVE — see README + src/config.h). A
// value stored in the config flash sector overrides these at boot.
// Mirrors firmware/steering/steering.ino in vanchor-ng: same command scale,
// endstops and loop constants, so the Pi-side behaviour is unchanged.
#ifndef STEER_RANGE_DEG
#define STEER_RANGE_DEG        360.0f  // soft endstops (cable wrap limit)
#endif
#ifndef STEER_FULL_SCALE_DEG
#define STEER_FULL_SCALE_DEG   180.0f  // CMD steer +-100 maps to +-180 deg
#endif
#ifndef STEER_KP
#define STEER_KP               6.0f
#endif
#ifndef STEER_KI
#define STEER_KI               0.8f
#endif
#ifndef STEER_KD
#define STEER_KD               0.6f
#endif
#ifndef STEER_INTEGRAL_LIMIT
#define STEER_INTEGRAL_LIMIT   120.0f  // clamp on Ki*integral, PWM units
#endif
#ifndef STEER_DEADBAND_DEG
#define STEER_DEADBAND_DEG     1.2f
#endif
#ifndef STEER_MIN_DRIVE_PWM
#define STEER_MIN_DRIVE_PWM    35      // stiction floor (0..255 scale)
#endif
#ifndef STEER_MAX_DRIVE_PWM
#define STEER_MAX_DRIVE_PWM    220     // cap (0..255 scale)
#endif
#ifndef STEER_STALL_ERR_DEG
#define STEER_STALL_ERR_DEG    4.0f
#endif
#ifndef STEER_STALL_MOVE_DEG
#define STEER_STALL_MOVE_DEG   1.0f
#endif
#ifndef STEER_STALL_TIME_MS
#define STEER_STALL_TIME_MS    600
#endif
#ifndef STEER_STALL_CURRENT_A
#define STEER_STALL_CURRENT_A  0.0f    // >0 enables current-based stall trip
#endif
#ifndef STEER_FAILSAFE_RECENTER
#define STEER_FAILSAFE_RECENTER 0      // hold (worm self-locks); 1 = recentre
#endif
#ifndef SRV_PWM_HZ
#define SRV_PWM_HZ             2000    // BTN8982 on-board bridge PWM
#endif

// AS5600 geometry: counts -> azimuth degrees. Magnet on the azimuth shaft,
// 1:1. Set ENC_INVERT if +PWM (starboard) decreases the reading.
#ifndef ENC_COUNTS_PER_REV
#define ENC_COUNTS_PER_REV     4096
#endif
#ifndef ENC_GEAR_RATIO
#define ENC_GEAR_RATIO         1.0f    // shaft revs per azimuth rev
#endif
#ifndef ENC_INVERT
#define ENC_INVERT             0
#endif
// Angle at the hall magnet (deg): 0.0 when the magnet marks dead-centre.
#ifndef HALL_ANGLE_DEG
#define HALL_ANGLE_DEG         0.0f
#endif
#ifndef HALL_DEBOUNCE_MS
#define HALL_DEBOUNCE_MS       50
#endif

// --------------------------------------------------------- thrust tuning --
// Mirrors firmware/engine/engine.ino semantics (slew, reverse dead-time,
// E-line states); the output stage is the BTN8982 bridge instead of a
// hijacked ESC.
#ifndef THR_SLEW_PER_S
#define THR_SLEW_PER_S         1.0f    // full scale per second
#endif
#ifndef THR_REVERSE_DEADTIME_MS
#define THR_REVERSE_DEADTIME_MS 1000
#endif
#ifndef THR_ZERO_EPS
#define THR_ZERO_EPS           0.02f
#endif

// Current-adaptive PWM schedule (boards/thrust-driver/README.md): high
// frequency where it is silent and cheap, lower as current rises.
//   amps:  0   5   10  15  20  25  30  40  50
//   kHz : 16  16  12   8   6   5   4   3   2
#ifndef THR_FREQ_HYST_A
#define THR_FREQ_HYST_A        2.0f    // hysteresis so the retune never hunts
#endif

// ------------------------------------------------------------- reporting --
#ifndef REPORT_A_MS
#define REPORT_A_MS            100     // steering feedback line, ~10 Hz
#endif
#ifndef REPORT_E_MS
#define REPORT_E_MS            200     // engine status line, ~5 Hz
#endif
#ifndef CONTROL_TICK_US
#define CONTROL_TICK_US        2000    // 500 Hz control loop
#endif

#endif // HELM_BOARD_H
